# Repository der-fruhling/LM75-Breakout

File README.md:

# LM75-Breakout
Breakout boards for LM75, TI TMP Series, and Some others

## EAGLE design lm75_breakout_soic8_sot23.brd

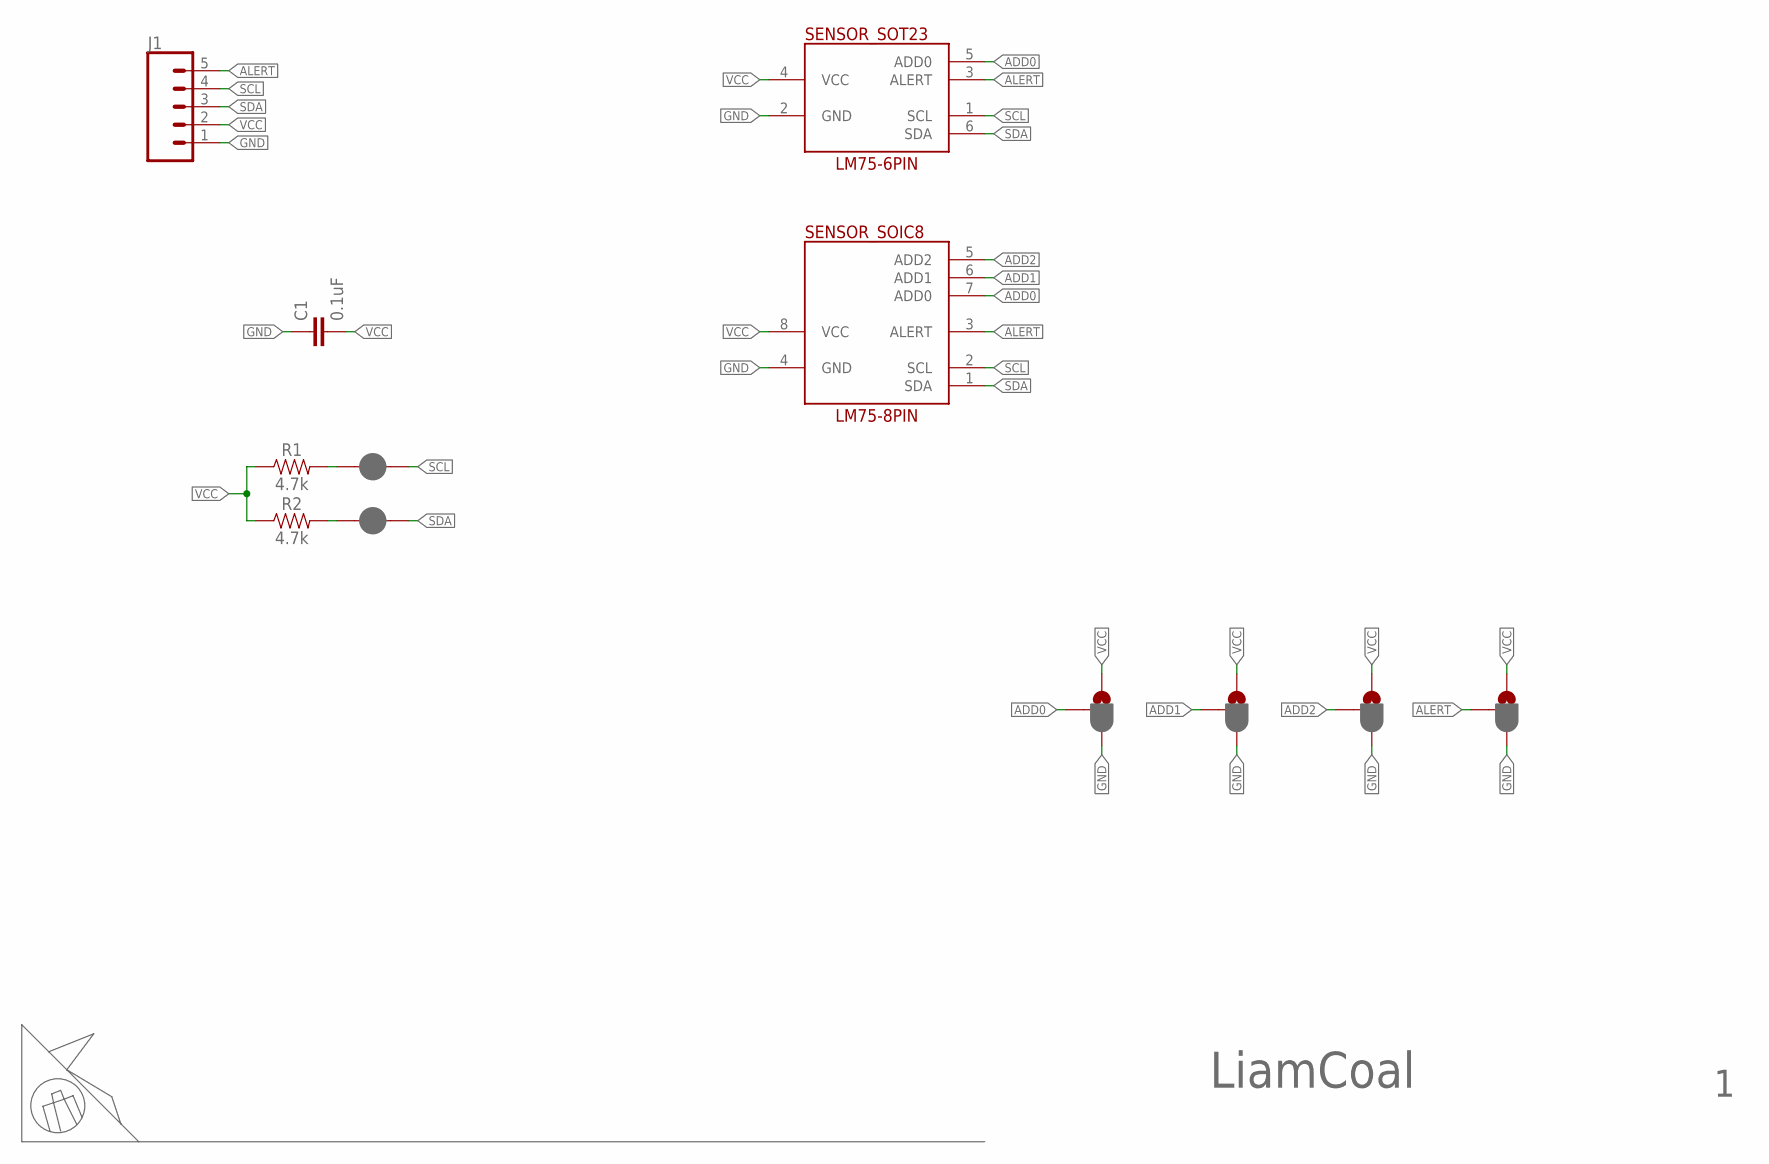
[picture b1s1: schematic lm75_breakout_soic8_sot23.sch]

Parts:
C1: 0.1uF; 0603
J1: CONN_05NO_SILK; 1X05_NO_SILK
JP1, JP2, JP3, JP6: JUMPER-SMT_3_1-NC_PASTE_SILK; SMT-JUMPER_3_1-NC_PASTE_SILK
JP4, JP5: JUMPER-SMT_2_NC_PASTE_SILK; SMT-JUMPER_2_NC_PASTE_SILK
R1, R2: 4.7k; 0603
SENSOR_SOIC8: LM75-8PIN; SOIC8
SENSOR_SOT23: LM75-6PIN; SOT23-6

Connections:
ADD0: JP1.2, SENSOR_SOIC8.7 (ADD0), SENSOR_SOT23.5 (ADD0)
ADD1: JP2.2, SENSOR_SOIC8.6 (ADD1)
ADD2: JP3.2, SENSOR_SOIC8.5 (ADD2)
ALERT: J1.5, JP6.2, SENSOR_SOIC8.3 (ALERT), SENSOR_SOT23.3 (ALERT)
GND: C1.1, J1.1, JP1.3, JP2.3, JP3.3, JP6.3, SENSOR_SOIC8.4 (GND), SENSOR_SOT23.2 (GND)
unnamed: JP4.1, R1.2
unnamed: JP5.1, R2.2
SCL: J1.4, JP4.2, SENSOR_SOIC8.2 (SCL), SENSOR_SOT23.1 (SCL)
SDA: J1.3, JP5.2, SENSOR_SOIC8.1 (SDA), SENSOR_SOT23.6 (SDA)
VCC: C1.2, J1.2, JP1.1, JP2.1, JP3.1, JP6.1, R1.1, R2.1, SENSOR_SOIC8.8 (VCC), SENSOR_SOT23.4 (VCC)

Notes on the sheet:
LiamCoal

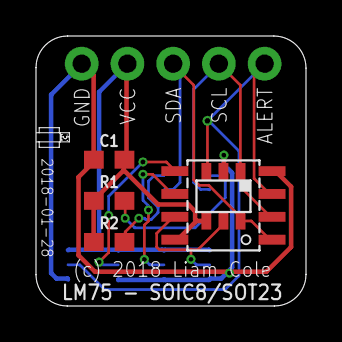
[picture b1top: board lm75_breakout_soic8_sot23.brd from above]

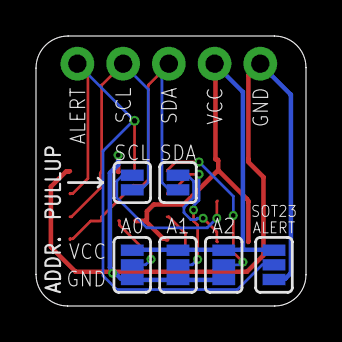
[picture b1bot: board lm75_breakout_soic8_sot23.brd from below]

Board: 2 copper layers, 15.0 x 15.0 mm, 12 parts (6 on the bottom side), 10 nets.

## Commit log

2018-02-19 Add files that we ordered for LM75 SOIC8/SOT23 breakout

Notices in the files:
lm75_breakout_soic8_sot23.brd:
(c) 2018 Liam Cole
parts and their libraries:
SparkFun-Jumpers: Licensing: Creative Commons ShareAlike 4.0 International - https://creativecommons.org/licenses/by-sa/4.0
